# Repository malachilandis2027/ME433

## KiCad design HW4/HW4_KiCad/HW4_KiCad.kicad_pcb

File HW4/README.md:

# HW4
## My board layout:

## My schematic:

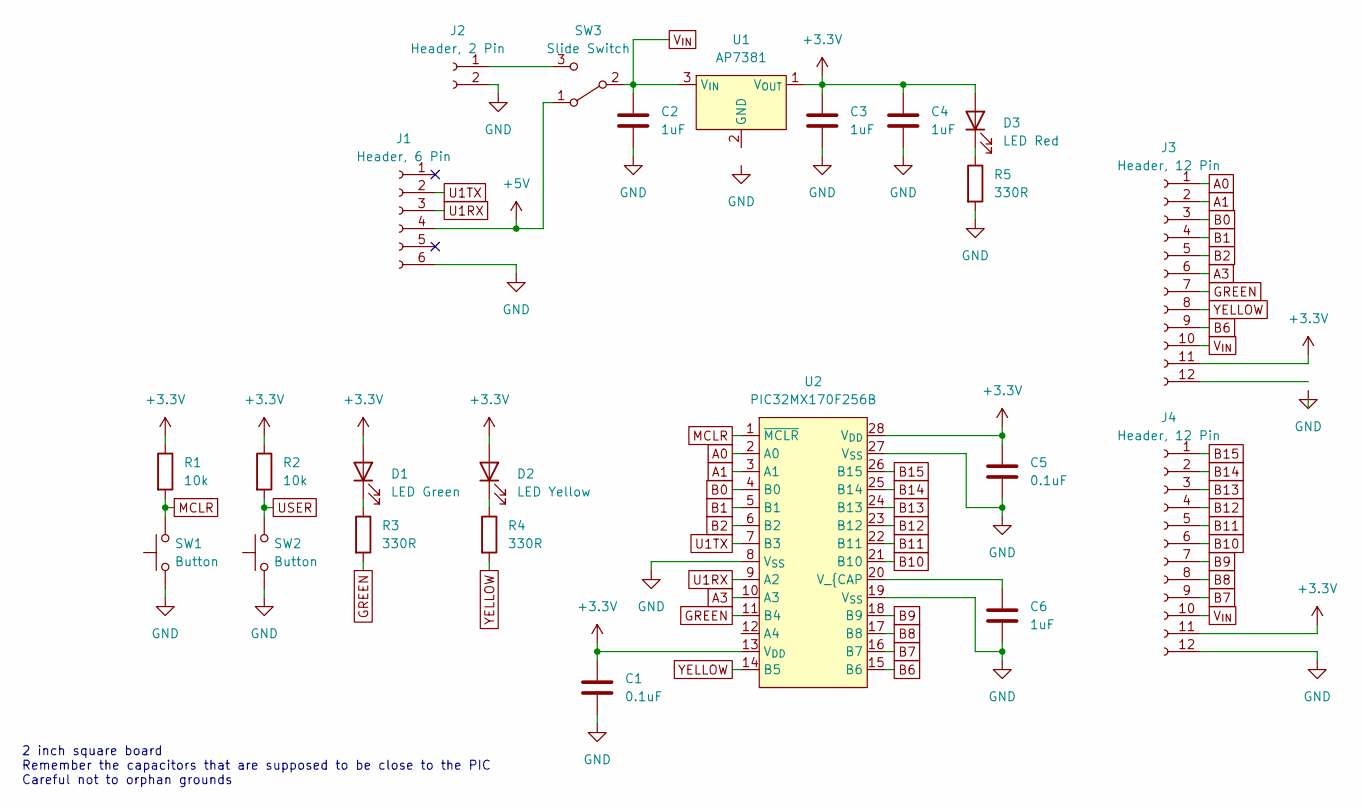
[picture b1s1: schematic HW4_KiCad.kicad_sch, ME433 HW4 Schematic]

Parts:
C1, C5: 0.1uF; Capacitor
C2, C3, C4, C6: 1uF; Capacitor
D1: LED Green; LED
D2: LED Yellow; LED
D3: LED Red; LED
J1: Header, 6 Pin; CP2102 Header
J2: Header, 2 Pin; Battery Connector
J3, J4: Header, 12 Pin; Side Header
R1, R2: 10k; Resistor
R3, R4, R5: 330R; Resistor
SW1, SW2: Button
SW3: Slide Switch; Switch
U1: AP7381
U2: PIC32MX170F256B; PIC Socket

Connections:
+3.3V: C1.1, C3.1, C4.1, C5.1, D1.2 (A), D2.2 (A), D3.2 (A), J3.11 (Pin_2), J4.11 (Pin_2), R1.1, R2.1, U1.1 (V_{OUT}), U2.13 (V_{DD}), U2.28 (V_{DD})
+5V: J1.4 (Pin_3), SW3.1 (A)
A0: J3.1 (Pin_12), U2.2 (A0)
A1: J3.2 (Pin_11), U2.3 (A1)
A3: J3.6 (Pin_7), U2.10 (A3)
B0: J3.3 (Pin_10), U2.4 (B0)
B1: J3.4 (Pin_9), U2.5 (B1)
B2: J3.5 (Pin_8), U2.6 (B2)
B6: J3.9 (Pin_4), U2.15 (B6)
B7: J4.9 (Pin_4), U2.16 (B7)
B8: J4.8 (Pin_5), U2.17 (B8)
B9: J4.7 (Pin_6), U2.18 (B9)
B10: J4.6 (Pin_7), U2.21 (B10)
B11: J4.5 (Pin_8), U2.22 (B11)
B12: J4.4 (Pin_9), U2.23 (B12)
B13: J4.3 (Pin_10), U2.24 (B13)
B14: J4.2 (Pin_11), U2.25 (B14)
B15: J4.1 (Pin_12), U2.26 (B15)
GND: C1.2, C2.2, C3.2, C4.2, C5.2, C6.2, J1.6 (Pin_1), J2.2 (Pin_1), J4.12 (Pin_1), R5.2, SW1.1, SW2.1, U2.8 (V_{SS}), U2.19 (V_{SS}), U2.27 (V_{SS})
GREEN: J3.7 (Pin_6), R3.2, U2.11 (B4)
MCLR: R1.2, SW1.2, U2.1 (~MCLR)
unnamed: C6.1, U2.20 (V_{CAP)
unnamed: D1.1 (K), R3.1
unnamed: D2.1 (K), R4.1
unnamed: D3.1 (K), R5.1
unnamed: J2.1 (Pin_2), SW3.3 (C)
U1RX: J1.3 (Pin_4), U2.9 (A2)
U1TX: J1.2 (Pin_5), U2.7 (B3)
USER: R2.2, SW2.2
V_{IN}: C2.1, J3.10 (Pin_3), J4.10 (Pin_3), SW3.2 (B), U1.3 (V_{IN})
YELLOW: J3.8 (Pin_5), R4.2, U2.14 (B5)

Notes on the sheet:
2 inch square board Remember the capacitors that are supposed to be close to the PIC Careful not to orphan grounds

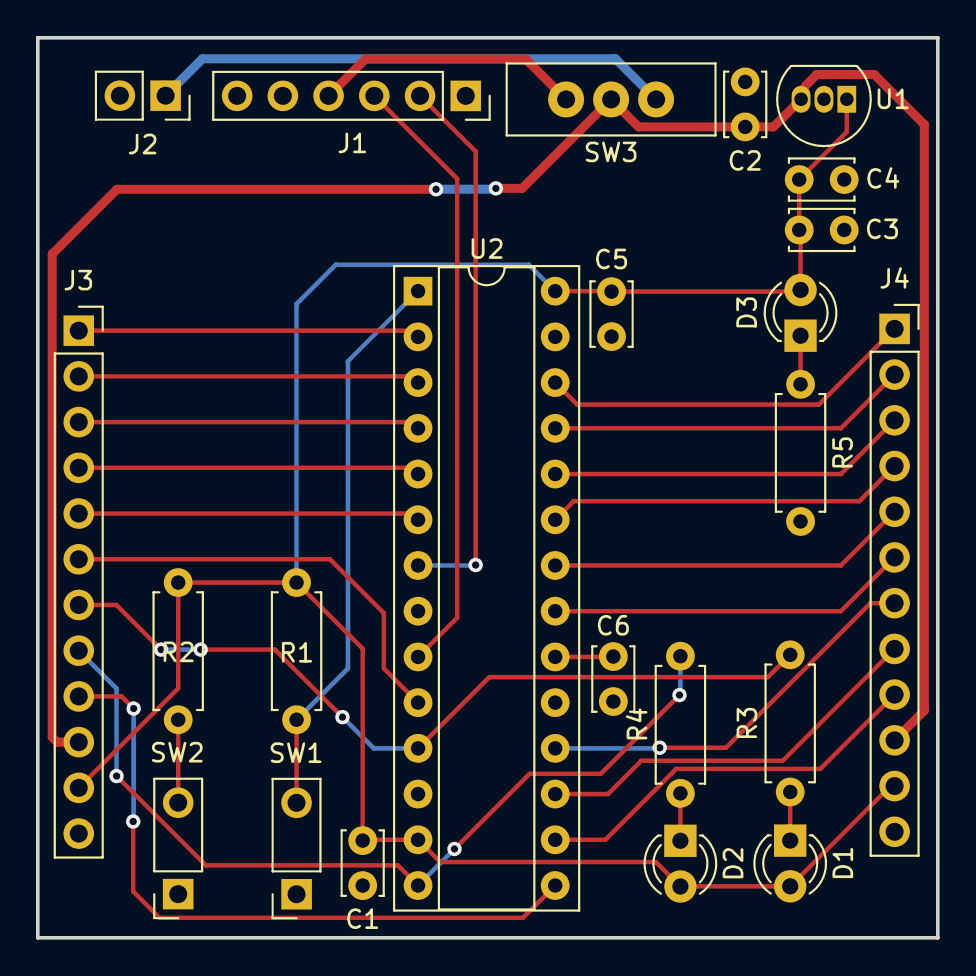
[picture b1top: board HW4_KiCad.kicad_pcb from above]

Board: 2 copper layers, 50.0 x 50.0 mm, 23 parts (0 on the bottom side), 31 nets.

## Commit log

2023-04-03 HW2 Folder Init
    Created HW2 folder, added some KiCad stuff
2023-04-04 Adding MPLAB project
2023-04-04 Modified template
2023-04-04 Added images of circuit and diagram
2023-04-04 Added link to demonstration video
2023-04-06 hw4 kicad start
2023-04-07 Adding HW3
2023-04-10 Updated plotter
2023-04-11 KiCad HW4 schematic
2023-04-17 hw4 update
2023-04-23 Updated hw5
2023-04-27 Modified kicad
2023-05-03 start hw9
2023-05-12 hw9 finished
2023-05-12 fix bug
2023-05-28 added hw5 image
2023-05-31 update code
2023-05-31 add private
2023-06-01 update HW6
2023-06-01 update HW7
2023-06-01 update HW8
2023-06-01 update hw10
2023-06-01 add readme to hw6
2023-06-01 fix hw6 readme :(
2023-06-01 add hw7 readme
2023-06-01 add hw8 readme
2023-06-01 add hw10 readme
2023-06-05 update hw4, add readme
2023-06-05 added schematic to hw4 readme
2023-06-05 add readme to hw12
2023-06-05 update hw11
2023-06-05 update hw13
2023-06-06 added hw15
2023-06-08 added hw14
2023-06-08 update hw12
2023-06-08 add hw14 readme
2023-06-08 update hw16
